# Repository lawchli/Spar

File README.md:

# Spar

**English** | [简体中文](README.zh-CN.md) | [日本語](README.ja.md)

Spar is a stereo line-in adapter for Android phones with a 5-pole headphone jack. It records a stereo line-level source, such as a synthesizer or a Eurorack module, through the phone's built-in audio codec, with no USB audio interface, while the headphone output remains available for monitoring.

A standard 4-pole (CTIA/OMTP) jack provides a single microphone input, so line-in adapters for it are limited to mono. A 5-pole jack adds a second microphone contact; Spar feeds the left and right channels into these two inputs.

**Development and test platform:** Sony Xperia XZ1 Compact, LineageOS 23.2 (Android 16), rooted.

## Features

- Stereo line input through the headphone jack, without a USB audio interface
- Low-latency monitoring: the input is looped back to the headphones inside the phone's audio codec, bypassing Android and apps
- Passive input network of four resistors, which can be built on the Spar board or [on a breadboard](pcb/breadboard/README.md)

## Performance

Measured on the breadboard prototype with a Korg NTS-1:

| Item | Value |
|---|---|
| Channels | 2 (stereo), headphone monitoring at the same time |
| Left/right separation | > 40 dB |
| Signal-to-noise ratio | approx. 65 dB |
| ADC gain | 12 (range 0–20, 1.5 dB per step) |
| Peak level, NTS-1 at full volume | approx. −13 dBFS |
| Input network, per channel | 10 kΩ series, 2.2 kΩ to ground |

Measurements of the finished board (THD+N, dynamic range, frequency response) will be published on the [`measurements`](../../tree/measurements) branch.

## Requirements

- An Android phone with a 5-pole headphone jack whose audio codec exposes a stereo (binaural) capture path
- Root access, for the mixer configuration and the capture tools
- Soldering tools, if you build the board yourself

## Repository layout

Each part of the project is developed on its own branch; `main` holds released snapshots.

| Branch | Contents |
|---|---|
| [`software`](../../tree/software) | Phone-side tools, scripts and setup notes |
| [`pcb`](../../tree/pcb) | Board: schematic, layout, fabrication files, BOM |
| [`enclosure`](../../tree/enclosure) | 3D-printed case |
| [`measurements`](../../tree/measurements) | Measurements of the finished device |

## To do

- [ ] Fabricate and assemble PCB Rev D
- [ ] Enclosure for Rev D
- [ ] Measurements on the finished device (THD+N, dynamic range, frequency response)
- [ ] Safe monitoring gain without feedback on the finished board
- [ ] One-step phone setup (Magisk module: start-up service, mixer configuration, recording control)
- [ ] Tests on other phones with a 5-pole jack

## License

[MIT](LICENSE) © LawChli. Third-party code keeps its own license (TinyALSA: BSD-3-Clause).

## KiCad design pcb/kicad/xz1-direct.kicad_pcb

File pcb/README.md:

# Spar PCB — Rev D

**Spar Rev D**, redrawn natively in EasyEDA Pro: **50.5 × 13.5 × 1.6 mm**, 2 layers, 0805 resistors, everything hand-solderable. The name comes from Iceland spar, the crystal that splits one image into two, as the board splits one 5-pole jack into monitoring and stereo recording.

## Circuit

The board is passive. A 5-pole plug goes into the phone; its poles are counted from the tip:

| Pole | Function | Connection |
|---|---|---|
| 1 | Left headphone | headphone jack tip |
| 2 | Right headphone | headphone jack ring |
| 3 | Left microphone | line-in tip through 10 kΩ, 2.2 kΩ to ground |
| 4 | Ground | both sleeves, star point |
| 5 | Right microphone | line-in ring through 10 kΩ, 2.2 kΩ to ground |

The 2.2 kΩ resistors give each microphone contact the DC load the phone needs to detect a headset microphone; the 10 kΩ series resistors drop line level to microphone level. Every ground branch (both jack sleeves and both 2.2 kΩ resistors) returns separately to the single ground pad of the plug wires, and neither copper layer has a pour. Background: [software/docs/STEREO-CAPTURE.md](../../../blob/software/software/docs/STEREO-CAPTURE.md).

## Board

Coordinates from the top-left corner of the component side, X right, Y down, in mm.

| Feature | Position |
|---|---|
| Jack axes (J1, J2) | (27.8, 6) and (39.8, 6), 12 mm apart |
| M2 mounting holes | (15.7, 10) and (47.8, 2.6): 2.2 mm non-plated, 2.6 mm copper keep-out radius on both sides |
| Lid-post notch | right edge, centre (48.5, 8.6), 6.6 mm cut-out, 7.2 mm keep-out |
| Wire pads | five pads at 2.54 mm pitch on a 55° row, one ground pad |

Checks in EasyEDA Pro: strict DRC 0 errors and 0 unrouted, 51 tracks, 8 vias, no copper pours; all 23 pins match the frozen netlist; four independent ground branches at the ground pad; minimum clearance between different nets 0.262 mm. Back silkscreen: Spar, Rev D.

Mounting: two flat low-profile M2 screws from the front with 0.5 mm nylon washers under the heads, nuts at the back.

## Files

| Path | Contents |
|---|---|
| `easyeda/Spar-RevD-layout.epro2` | Complete EasyEDA Pro project (schematic, PCB and libraries); import it in EasyEDA Pro |
| `easyeda/Spar-FivePole-Wires.elibz2` | Library for the five-wire pad component |
| `easyeda/Spar-RevD-layout.epcb` | PCB source (JSON) |
| `easyeda/*.enet` | Netlists exported from the PCB and the schematic |
| `previews/` | Renders exported from EasyEDA Pro |
| `BOM.csv` | Parts for one board |

Fabrication files (Gerbers, drill files) will be added when the board is ordered. If the manufacturer's review requires changes, they will become Rev E.

## Revisions

Each revision replaces the previous one on this branch; earlier ones are kept as tags.

| Tag | Date | Revision |
|---|---|---|
| [`pcb-breadboard`](../../../tree/pcb-breadboard/pcb) | 2026-10-11 | Breadboard / hand-wired build |
| [`pcb-rev-a`](../../../tree/pcb-rev-a/pcb) | 2026-10-13 | Cable splitter board, 35 × 15 mm (KiCad) |
| [`pcb-rev-b`](../../../tree/pcb-rev-b/pcb) | 2026-10-15 | Direct-plug board, 48 × 13.5 mm (KiCad) |
| [`pcb-rev-b-m2`](../../../tree/pcb-rev-b-m2/pcb) | 2026-10-16 | Rev B with two M2 mounting holes (KiCad) |
| [`pcb-rev-c-m2`](../../../tree/pcb-rev-c-m2/pcb) | 2026-10-18 | Jacks grouped next to the plug (KiCad) |
| [`pcb-rev-d`](../../../tree/pcb-rev-d/pcb) | 2026-10-20 | Spar Rev D, redrawn in EasyEDA Pro |

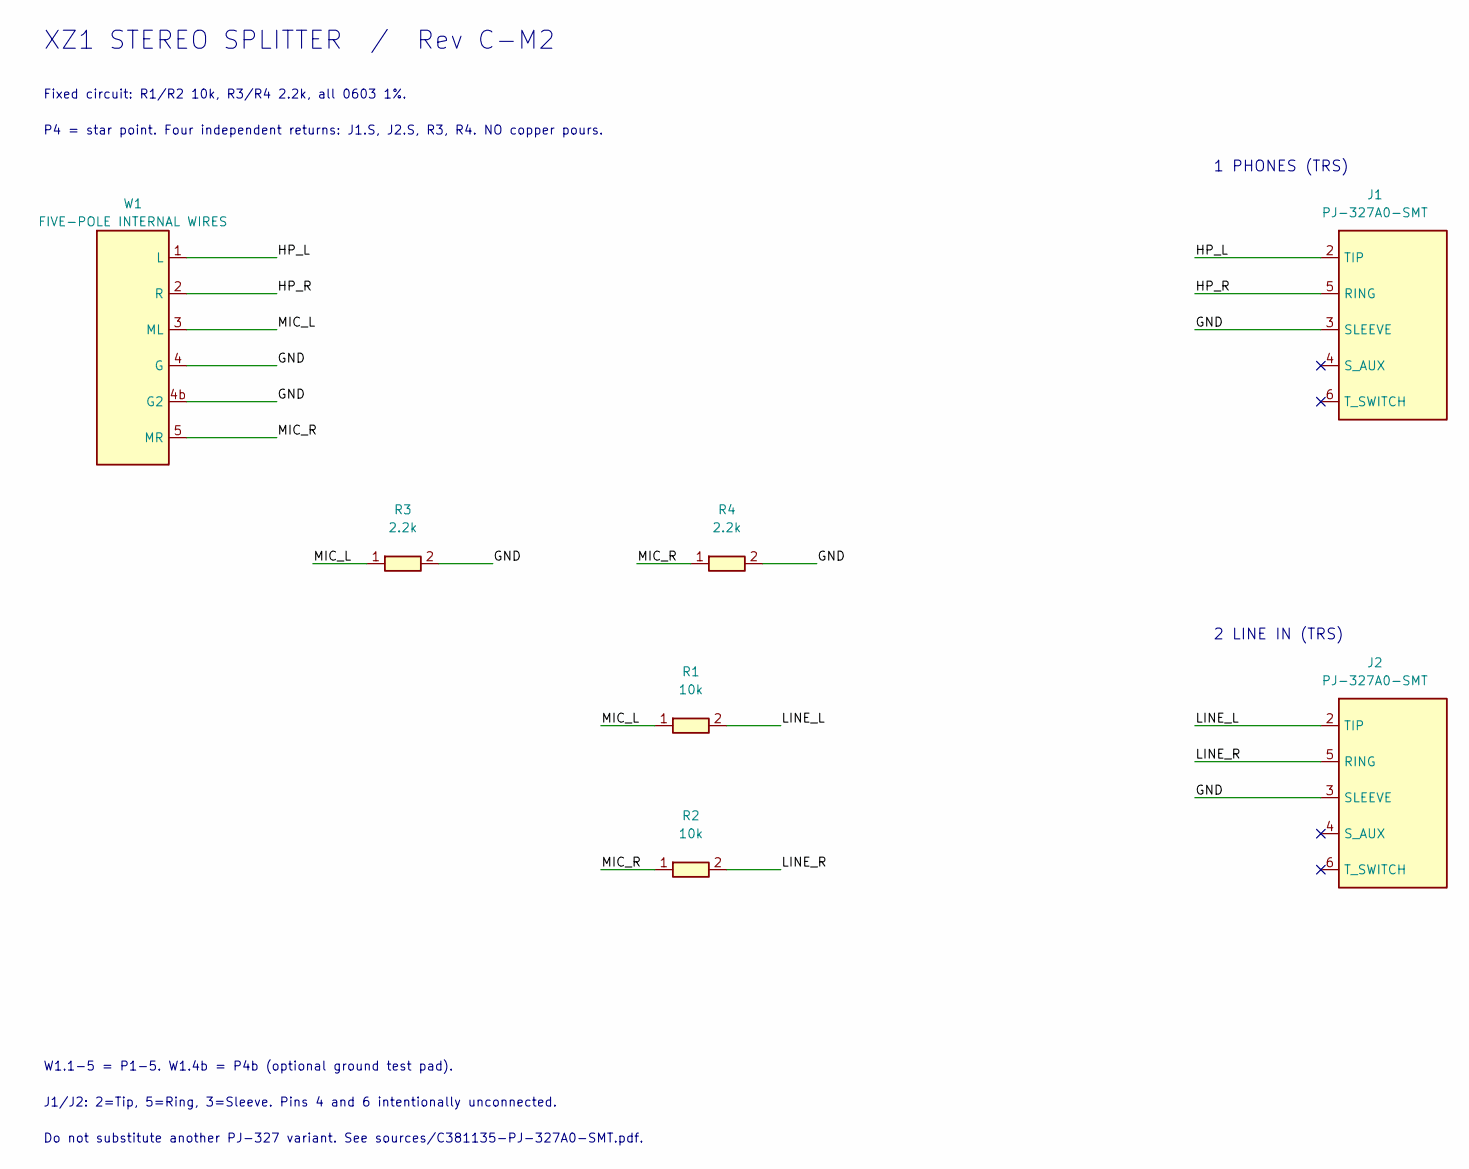
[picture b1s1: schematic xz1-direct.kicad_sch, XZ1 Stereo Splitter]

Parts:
J1, J2: PJ-327A0-SMT; PJ-327A0-SMT_C381135; LCSC C381135
R1, R2: 10k; R_0603_1608Metric; LCSC C25804
R3, R4: 2.2k; R_0603_1608Metric; LCSC C4190
W1: FIVE-POLE INTERNAL WIRES; WirePads_5Pole_Star

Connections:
/GND: J1.3 (SLEEVE), J2.3 (SLEEVE), R3.2, R4.2, W1.4 (G), W1.4b (G2)
/HP_L: J1.2 (TIP), W1.1 (L)
/HP_R: J1.5 (RING), W1.2 (R)
/LINE_L: J2.2 (TIP), R1.2
/LINE_R: J2.5 (RING), R2.2
/MIC_L: R1.1, R3.1, W1.3 (ML)
/MIC_R: R2.1, R4.1, W1.5 (MR)

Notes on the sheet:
XZ1 STEREO SPLITTER / Rev C-M2
Fixed circuit: R1/R2 10k, R3/R4 2.2k, all 0603 1%.
P4 = star point. Four independent returns: J1.S, J2.S, R3, R4. NO copper pours.
1 PHONES (TRS)
2 LINE IN (TRS)
W1.1-5 = P1-5. W1.4b = P4b (optional ground test pad).
J1/J2: 2=Tip, 5=Ring, 3=Sleeve. Pins 4 and 6 intentionally unconnected.
Do not substitute another PJ-327 variant. See sources/C381135-PJ-327A0-SMT.pdf.

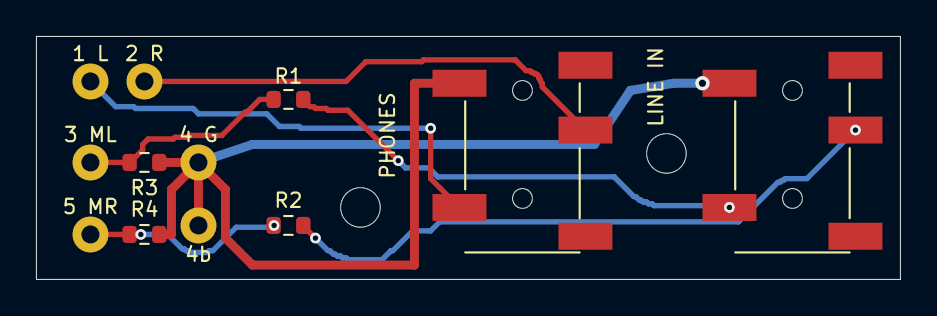
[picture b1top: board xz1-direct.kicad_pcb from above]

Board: 2 copper layers, 48.0 x 13.5 mm, 7 parts (0 on the bottom side), 7 nets.

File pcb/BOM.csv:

Ref,Qty,Part,Manufacturer part,LCSC,Notes
J1 J2,2,"3.5 mm TRS socket, SMD",XKB PJ-327A0-SMT,C381135,Hand-soldered
R1 R2,2,"10 kΩ 1 %, 0805",0805W8F1002T5E,C17414,Series resistors
R3 R4,2,"2.2 kΩ 1 %, 0805",0805W8F2201T5E,C17520,Detection load to ground
—,1,"5-pole 3.5 mm plug, wire terminals",—,—,Wired to the five pads; poles counted from the tip
—,2,"M2 screw, flat low-profile head ≤ 5 mm, length to suit the enclosure",—,—,From the front through the mounting holes
—,2,"M2 hex nut, 4 mm across flats",—,—,At the back
—,2,"M2 nylon flat washer, 0.5 mm",—,—,Under the screw heads to protect the solder mask
